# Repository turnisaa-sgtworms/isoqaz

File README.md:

This is based on a Kicad Template project (that also happens to be a dev-board) for the STM32F072CBT6.

****I used this video for turning this template into a BlackPill-compatible dev board:**** https://youtu.be/LvX-Us9VZM0

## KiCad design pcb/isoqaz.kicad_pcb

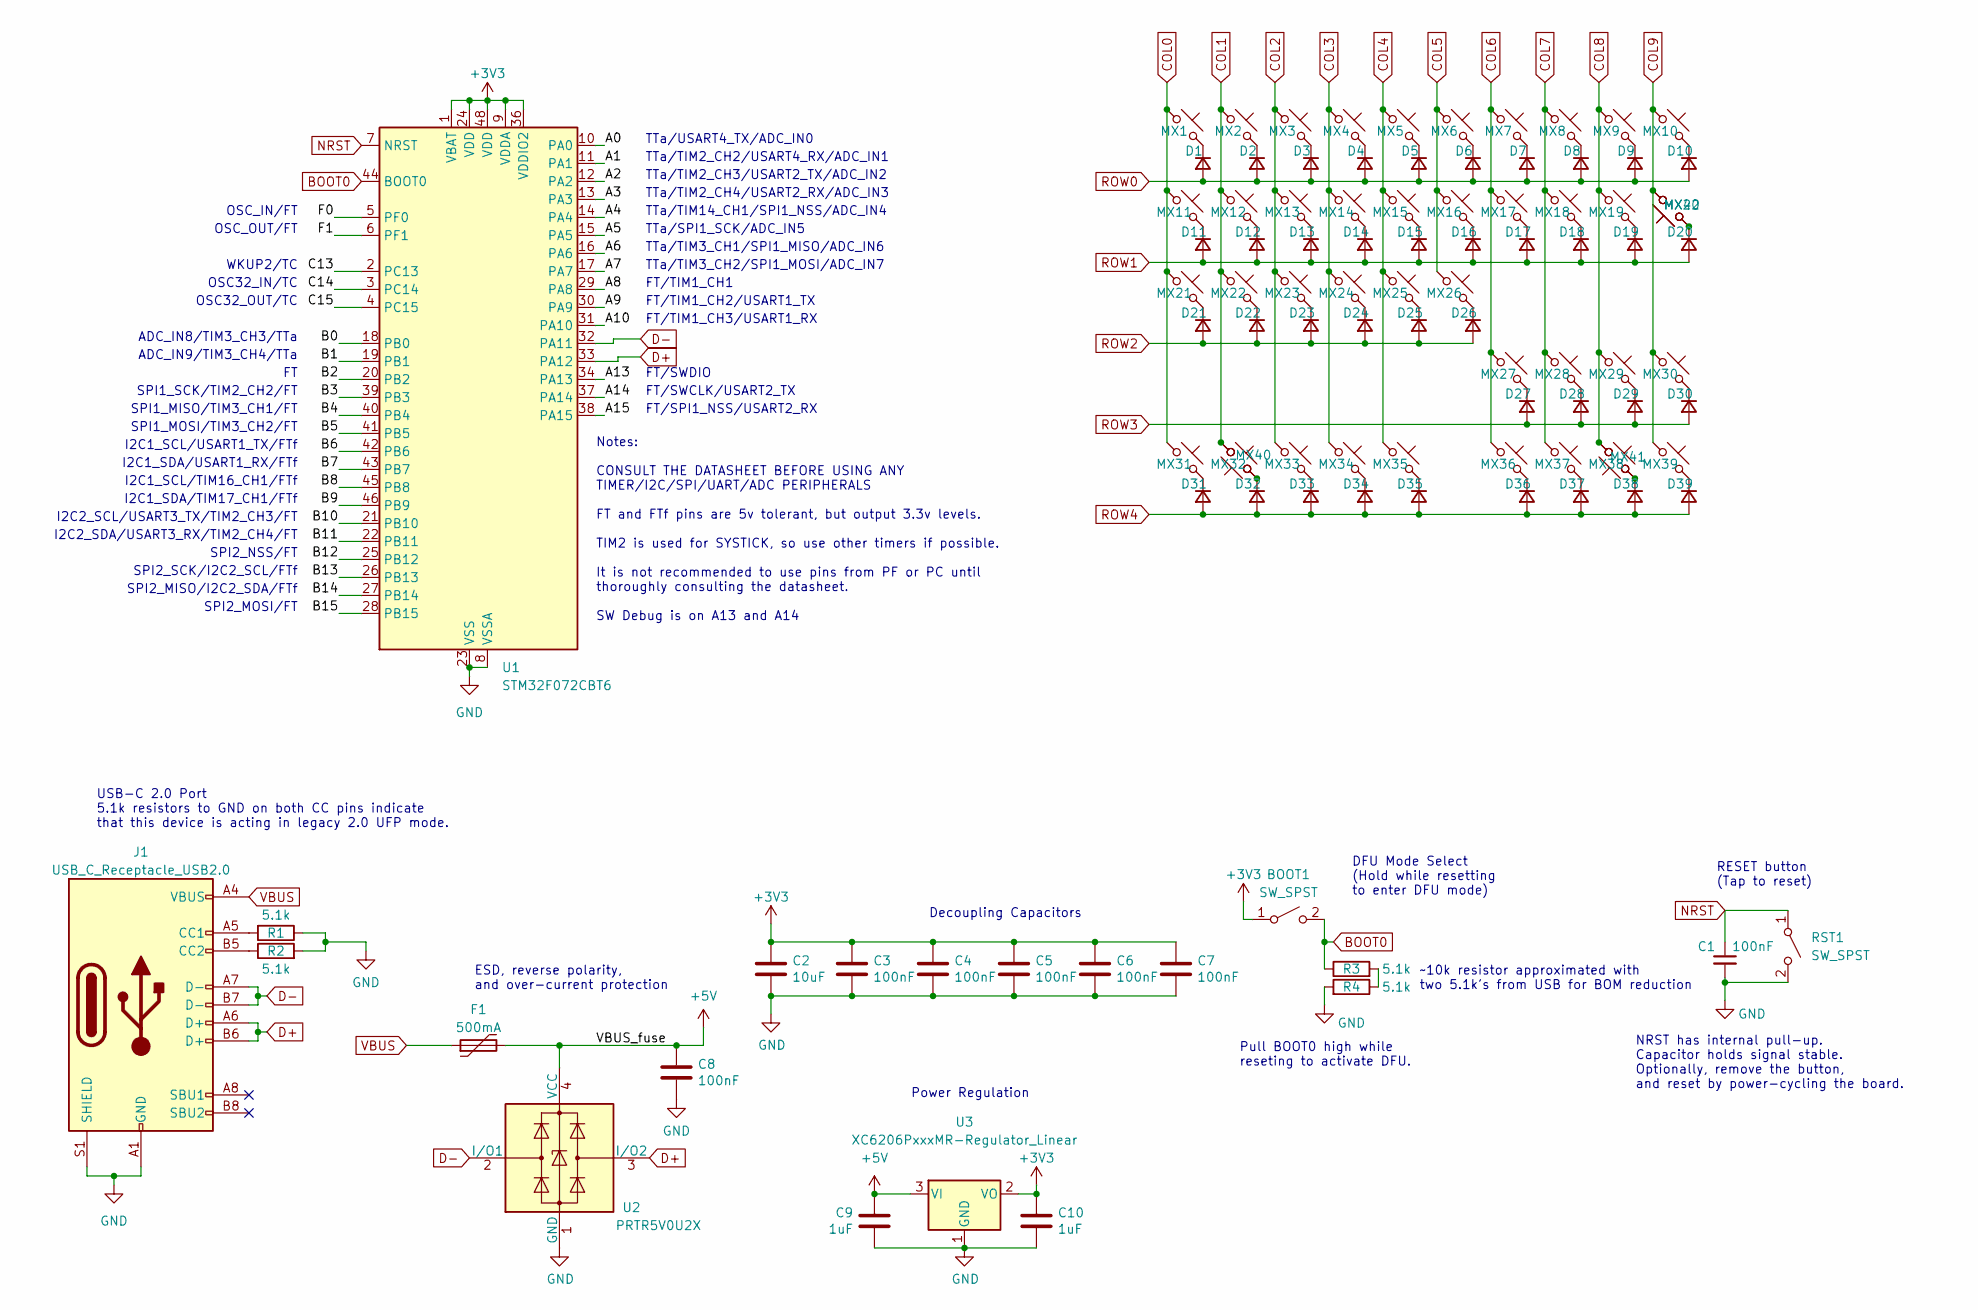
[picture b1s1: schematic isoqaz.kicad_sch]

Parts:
BOOT1: SW_SPST; SW_SPST_TL3342
C1, C3, C4, C5, C6, C7, C8: 100nF; C_0402_1005Metric; LCSC C307331
C2: 10uF; C_0603_1608Metric; LCSC C307331
C9, C10: 1uF; C_0402_1005Metric; LCSC C307331
D1, D2, D3, D4, D5, D6, D7, D8, D9, D10, D11, D12, D13, D14, D15, D16, D17, D18, D19, D20, D21, D22, D23, D24, D25, D26, D27, D28, D29, D30, D31, D32, D33, D34, D35, D36, D37, D38, D39: D_Small; D_SOD-123
F1: 500mA; Fuse_1206_3216Metric; LCSC C135341
J1: USB_C_Receptacle_USB2.0; USB_C_Receptacle_HRO_TYPE-C-31-M-12; JlcRotOffset 180
MX1, MX2, MX3, MX4, MX5, MX6, MX7, MX8, MX9, MX10, MX11, MX12, MX13, MX14, MX15, MX16, MX17, MX18, MX19, MX20, MX21, MX22, MX23, MX24, MX25, MX26, MX27, MX28, MX29, MX30, MX31, MX32, MX33, MX34, MX35, MX36, MX37, MX38, MX39, MX40, MX41, MX42: MX_SW_HS; SW_MX_HS_CPG151101S11_1u
R1, R2, R3, R4: 5.1k; R_0402_1005Metric
RST1: SW_SPST; SW_SPST_TL3342
U1: STM32F072CBT6; LQFP-48_7x7mm_P0.5mm; JlcRotOffset 90
U2: PRTR5V0U2X; SOT-143; LCSC C2827688
U3: XC6206PxxxMR-Regulator_Linear; SOT-23; LCSC C5446

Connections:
+3V3: BOOT1.1 (A), C2.1, C3.1, C4.1, C5.1, C6.1, C7.1, C10.1, U1.1 (VBAT), U1.9 (VDDA), U1.24 (VDD), U1.36 (VDDIO2), U1.48 (VDD), U3.2 (VO)
+5V: C8.1, C9.1, F1.2, U2.4 (VCC), U3.3 (VI)
/A0: U1.10 (PA0)
/A1: U1.11 (PA1)
/A2: U1.12 (PA2)
/A3: U1.13 (PA3)
/A4: U1.14 (PA4)
/A5: U1.15 (PA5)
/A6: U1.16 (PA6)
/A7: U1.17 (PA7)
/A8: U1.29 (PA8)
/A9: U1.30 (PA9)
/A10: U1.31 (PA10)
/A13: U1.34 (PA13)
/A14: U1.37 (PA14)
/A15: U1.38 (PA15)
/B0: U1.18 (PB0)
/B1: U1.19 (PB1)
/B2: U1.20 (PB2)
/B3: U1.39 (PB3)
/B4: U1.40 (PB4)
/B5: U1.41 (PB5)
/B6: U1.42 (PB6)
/B7: U1.43 (PB7)
/B8: U1.45 (PB8)
/B9: U1.46 (PB9)
/B10: U1.21 (PB10)
/B11: U1.22 (PB11)
/B12: U1.25 (PB12)
/B13: U1.26 (PB13)
/B14: U1.27 (PB14)
/B15: U1.28 (PB15)
/C13: U1.2 (PC13)
/C14: U1.3 (PC14)
/C15: U1.4 (PC15)
/F0: U1.5 (PF0)
/F1: U1.6 (PF1)
BOOT0: BOOT1.2 (B), R3.1, U1.44 (BOOT0)
COL0: MX1.1, MX11.1, MX21.1, MX31.1
COL1: MX2.1, MX12.1, MX22.1, MX32.1, MX40.2
COL2: MX3.1, MX13.1, MX23.1, MX33.1
COL3: MX4.1, MX14.1, MX24.1, MX34.1
COL4: MX5.1, MX15.1, MX25.1, MX35.1
COL5: MX6.1, MX16.1, MX26.1
COL6: MX7.1, MX17.1, MX27.1, MX36.1
COL7: MX8.1, MX18.1, MX28.1, MX37.1
COL8: MX9.1, MX19.1, MX29.1, MX38.1, MX41.2
COL9: MX10.1, MX20.2, MX30.1, MX39.1, MX42.2
D+: J1.A6 (D+), J1.B6 (D+), U1.33 (PA12), U2.3 (I/O2)
D-: J1.A7 (D-), J1.B7 (D-), U1.32 (PA11), U2.2 (I/O1)
GND: C1.2, C2.2, C3.2, C4.2, C5.2, C6.2, C7.2, C8.2, C9.2, C10.2, J1.A1 (GND), J1.A12 (GND), J1.B1 (GND), J1.B12 (GND), J1.S1 (SHIELD), R1.1, R2.2, R4.2, RST1.2 (B), U1.8 (VSSA), U1.23 (VSS), U1.35 (VSS), U1.47 (VSS), U2.1 (GND), U3.1 (GND)
NRST: C1.1, RST1.1 (A), U1.7 (NRST)
unnamed: D1.1 (K), MX1.2
unnamed: D2.1 (K), MX2.2
unnamed: D3.1 (K), MX3.2
unnamed: D4.1 (K), MX4.2
unnamed: D5.1 (K), MX5.2
unnamed: D6.1 (K), MX6.2
unnamed: D7.1 (K), MX7.2
unnamed: D8.1 (K), MX8.2
unnamed: D9.1 (K), MX9.2
unnamed: D10.1 (K), MX10.2
unnamed: D11.1 (K), MX11.2
unnamed: D12.1 (K), MX12.2
unnamed: D13.1 (K), MX13.2
unnamed: D14.1 (K), MX14.2
unnamed: D15.1 (K), MX15.2
unnamed: D16.1 (K), MX16.2
unnamed: D17.1 (K), MX17.2
unnamed: D18.1 (K), MX18.2
unnamed: D19.1 (K), MX19.2
unnamed: D20.1 (K), MX20.1, MX42.1
unnamed: D21.1 (K), MX21.2
unnamed: D22.1 (K), MX22.2
unnamed: D23.1 (K), MX23.2
unnamed: D24.1 (K), MX24.2
unnamed: D25.1 (K), MX25.2
unnamed: D26.1 (K), MX26.2
unnamed: D27.1 (K), MX27.2
unnamed: D28.1 (K), MX28.2
unnamed: D29.1 (K), MX29.2
unnamed: D30.1 (K), MX30.2
unnamed: D31.1 (K), MX31.2
unnamed: D32.1 (K), MX32.2, MX40.1
unnamed: D33.1 (K), MX33.2
unnamed: D34.1 (K), MX34.2
unnamed: D35.1 (K), MX35.2
unnamed: D36.1 (K), MX36.2
unnamed: D37.1 (K), MX37.2
unnamed: D38.1 (K), MX38.2, MX41.1
unnamed: D39.1 (K), MX39.2
unnamed: J1.A5 (CC1), R1.2
unnamed: J1.B5 (CC2), R2.1
unnamed: R3.2, R4.1
ROW0: D1.2 (A), D2.2 (A), D3.2 (A), D4.2 (A), D5.2 (A), D6.2 (A), D7.2 (A), D8.2 (A), D9.2 (A), D10.2 (A)
ROW1: D11.2 (A), D12.2 (A), D13.2 (A), D14.2 (A), D15.2 (A), D16.2 (A), D17.2 (A), D18.2 (A), D19.2 (A), D20.2 (A)
ROW2: D21.2 (A), D22.2 (A), D23.2 (A), D24.2 (A), D25.2 (A), D26.2 (A)
ROW3: D27.2 (A), D28.2 (A), D29.2 (A), D30.2 (A)
ROW4: D31.2 (A), D32.2 (A), D33.2 (A), D34.2 (A), D35.2 (A), D36.2 (A), D37.2 (A), D38.2 (A), D39.2 (A)
VBUS: F1.1, J1.A4 (VBUS), J1.A9 (VBUS), J1.B4 (VBUS), J1.B9 (VBUS)

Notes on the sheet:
SPI1_SCK/TIM2_CH2/FT
FT/TIM1_CH1
FT/TIM1_CH3/USART1_RX
SPI2_NSS/FT
Notes: CONSULT THE DATASHEET BEFORE USING ANY TIMER/I2C/SPI/UART/ADC PERIPHERALS FT and FTf pins are 5v tolerant, but output 3.3v levels. TIM2 is used for SYSTICK, so use other timers if possible. It is not recommended to use pins from PF or PC until thoroughly consulting the datasheet. SW Debug is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
TTa/TIM2_CH4/USART2_RX/ADC_IN3
NRST has internal pull-up. Capacitor holds signal stable. Optionally, remove the button, and reset by power-cycling the board.
FT/SWDIO
Decoupling Capacitors
SPI1_MOSI/TIM3_CH2/FT
ADC_IN9/TIM3_CH4/TTa
I2C2_SCL/USART3_TX/TIM2_CH3/FT
SPI2_MISO/I2C2_SDA/FTf
FT/SWCLK/USART2_TX
I2C1_SCL/TIM16_CH1/FTf
~10k resistor approximated with two 5.1k's from USB for BOM reduction
TTa/TIM2_CH2/USART4_RX/ADC_IN1
USB-C 2.0 Port 5.1k resistors to GND on both CC pins indicate that this device is acting in legacy 2.0 UFP mode.
TTa/TIM2_CH3/USART2_TX/ADC_IN2
OSC_IN/FT
DFU Mode Select (Hold while resetting to enter DFU mode)
WKUP2/TC
I2C2_SDA/USART3_RX/TIM2_CH4/FT
ADC_IN8/TIM3_CH3/TTa
RESET button (Tap to reset)
Pull BOOT0 high while reseting to activate DFU.
I2C1_SDA/TIM17_CH1/FTf
TTa/SPI1_SCK/ADC_IN5
TTa/TIM3_CH1/SPI1_MISO/ADC_IN6
TTa/TIM3_CH2/SPI1_MOSI/ADC_IN7
OSC32_OUT/TC
FT/SPI1_NSS/USART2_RX
SPI1_MISO/TIM3_CH1/FT
OSC32_IN/TC
TTa/TIM14_CH1/SPI1_NSS/ADC_IN4
I2C1_SDA/USART1_RX/FTf
SPI2_MOSI/FT
FT/TIM1_CH2/USART1_TX
Power Regulation
SPI2_SCK/I2C2_SCL/FTf

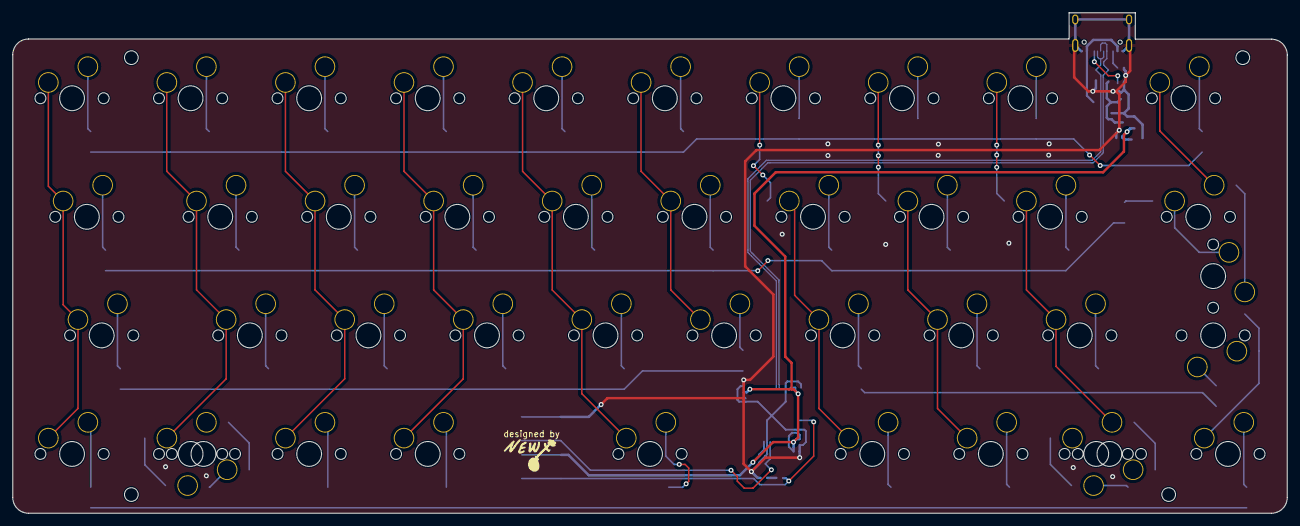
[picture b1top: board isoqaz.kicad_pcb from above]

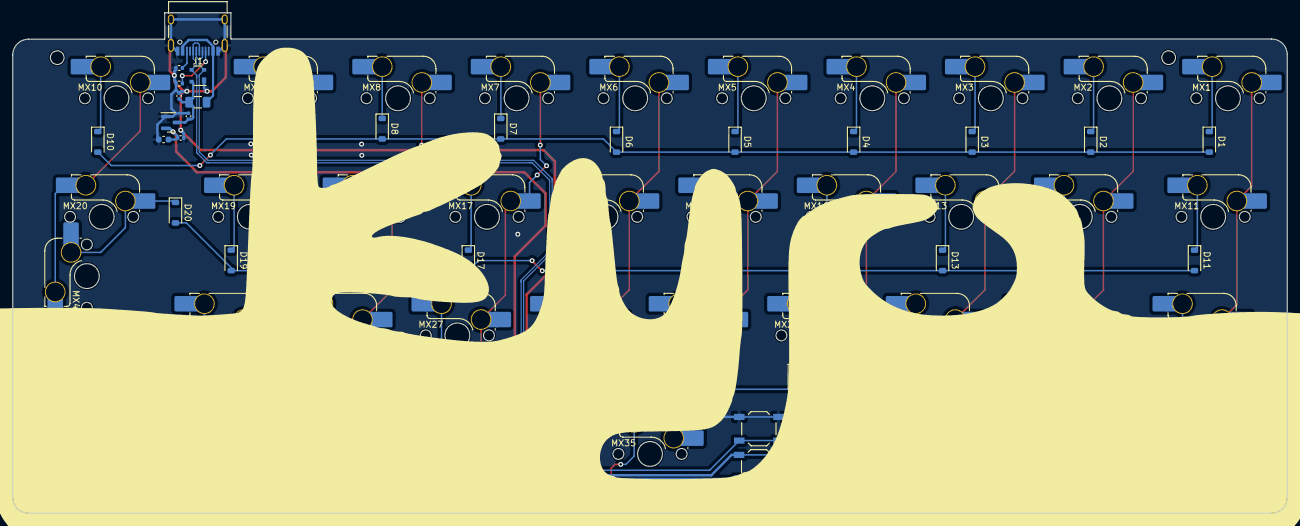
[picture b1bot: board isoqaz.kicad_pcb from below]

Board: 2 copper layers, 204.8 x 80.4 mm, 102 parts (102 on the bottom side), 65 nets.

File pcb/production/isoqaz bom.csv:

Designator,Footprint,Quantity,Value,LCSC Part #
"BOOT1, RST1",SW_SPST_TL3342,2,SW_SPST,C318884
"C1, C3, C4, C5, C6, C7, C8",402,7,100nF,C307331
"C10, C9",402,2,1uF,C52923
C2,603,1,10uF,C19702
"D1, D10, D11, D12, D13, D14, D15, D16, D17, D18, D19, D2, D20, D21, D22, D23, D24, D25, D26, D27, D28, D29, D3, D30, D31, D32, D33, D34, D35, D36, D37, D38, D39, D4, D5, D6, D7, D8, D9",D_SOD-123,39,D_Small,C81598
F1,1206,1,500mA,C369160
J1,USB_C_Receptacle_HRO_TYPE-C-31-M-12,1,USB_C_Receptacle_USB2.0,C165948
"MX1, MX10, MX11, MX12, MX13, MX14, MX15, MX16, MX17, MX18, MX19, MX2, MX20, MX21, MX22, MX23, MX24, MX25, MX26, MX27, MX28, MX29, MX3, MX30, MX31, MX32, MX33, MX34, MX35, MX36, MX37, MX38, MX39, MX4, MX40, MX41, MX42, MX5, MX6, MX7, MX8, MX9",SW_MX_HS_CPG151101S11_1u,42,MX_SW_HS,CPG151101S11-16
"R1, R2, R3, R4",402,4,5.1k,C25905
U1,LQFP-48_7x7mm_P0.5mm,1,STM32F072CBT6,C81720
U2,SOT-143,1,PRTR5V0U2X,C2827688
U3,SOT-23,1,XC6206PxxxMR-Regulator_Linear,C5446

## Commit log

2025-06-06 added case files, finished pcb
2025-07-26 added milled case, reorganized files
